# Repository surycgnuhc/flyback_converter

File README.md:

# Flyback Switching Power Supply

Design and simulation work for an isolated flyback switching power supply.

The project is being developed in two stages: a **low-voltage development prototype** for safe simulation and learning, followed by adaptation to the final universal AC input specification.

## Development Prototype Specifications

| Parameter           | Value   |
| ------------------- | ------- |
| Input               | 24 VDC  |
| Output              | 12 V    |
| Output power        | 24 W    |
| Output current      | 2 A     |
| Switching frequency | 100 kHz |
| Efficiency target   | 85%     |
| Regulation          | ±5%     |
| Isolation           | Yes     |

The low-voltage input is being used during the initial flyback design and simulation to avoid working with the high-voltage DC bus produced by an AC mains rectifier.

The output remains fixed at **12 V / 2 A** for this version. An adjustable-output version is planned as a future iteration.

## Final Target Specifications

| Parameter           | Value      |
| ------------------- | ---------- |
| Input               | 90–264 VAC |
| Input frequency     | 60 Hz      |
| Output              | 12 V       |
| Output power        | 24 W       |
| Output current      | 2 A        |
| Switching frequency | 100 kHz    |
| Efficiency target   | 85%        |
| Regulation          | ±5%        |
| Isolation           | Yes        |

The final version will use a universal AC input with a bridge rectifier, bulk capacitor, inrush-current limiting, and isolated flyback converter.

## Project Status

Currently paralleling the design process between kicad and ltspice simulation 

### Low-Voltage Flyback Development

* [ ] Low-voltage input stage — 24 VDC
* [ ] Flyback transformer design
* [ ] Primary-side switch + controller selection
* [ ] Secondary-side rectification + output filtering
* [ ] Feedback/compensation loop
* [ ] Efficiency and regulation validation

### Final AC Input Version

* [x] Bridge rectifier + bulk capacitor front-end — designed and simulated in LTspice
* [ ] Inrush current limiting (NTC/fuse)
* [ ] Adapt flyback design for ~126–373 VDC bus
* [ ] Primary-side switch + controller selection
* [ ] Secondary-side rectification + output filtering
* [ ] Feedback/compensation loop
* [ ] PCB layout

## Repo Structure

```text
/reports   - Written validation summaries with simulation screenshots
/sim       - LTspice schematic (.asc) and simulation files
```

## Reports

* [Rectifier & Bulk Capacitor Stage Validation](reports/rectifier_stage_validation_summary.md)

## Tools

* LTspice (schematic capture and simulation)

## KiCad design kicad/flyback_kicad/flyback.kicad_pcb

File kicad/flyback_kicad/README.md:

# Flyback KiCad project: 24V in, 12V/2A out, 100kHz

Power stage only, ported from the validated LTspice circuit. Made in KiCad 7 format. KiCad 8 and 9 open it and offer to upgrade the files: click Yes.

## Open it
1. Unzip the folder and keep every file together.
2. KiCad > File > Open Project > `flyback.kicad_pro`.
3. Double-click `flyback.kicad_sch` (schematic) or `flyback.kicad_pcb` (board).

## Get to a printable PCB
1. Schematic: double-click T1, set the Footprint field (see gaps below).
2. References (R1, C1 ...) are already set, no annotation needed.
3. PCB Editor: Tools > Update PCB from Schematic (F8) > Update PCB. All footprints and nets load; click to drop them on the board.
4. Place parts, then route with X. Keep GND_PRI and GND_SEC separate.
5. Draw the board outline on layer Edge.Cuts (Place > Line, then close the shape).
6. File > Print, or File > Plot for Gerbers.

## Nets (matches LTspice)
| Net | Pins |
|---|---|
| VIN | J1.1, T1.1 (dot), C3.1, R1.1 |
| GND_PRI | J1.2, J3.2, Q1.S (1-3), R3.2 |
| DRAIN | T1.2, Q1.D (5-8), D2 anode |
| SNUB | D2 cathode, C3.2, R1.2 |
| SEC_AC | T1.4, D1 anode |
| VOUT | D1 cathode, C1+, C2+, J2.1 |
| GND_SEC | T1.3 (dot), C1-, C2-, J2.2 |
| GATE_DRV | J3.1, R2.1 |
| GATE | R2.2, Q1.G (4), R3.1 |

## Parts
| Ref | Part | Footprint |
|---|---|---|
| Q1 | MCQ15N10YA-TP | SOIC-8 (S=1-3, G=4, D=5-8, from MCC datasheet) |
| D1 | 1N5822 Schottky | DO-201AD |
| D2 | UF4007 | DO-41 |
| C1, C2 | 47uF/25V electrolytic | Radial D6.3mm, pin 1 = + |
| C3 | 560nF/100V film | Rect 7.2 x 5.5mm, 5mm pitch |
| R1 | 390 ohm, 5W | Axial power 22.4mm |
| R2, R3 | 10 ohm, 10k | Axial DIN0207 |
| J1, J2 | 2-pin terminal block | 5.08mm |
| J3 | 2-pin header (gate drive in) | 2.54mm |
| T1 | Lp 20.7uH, Np:Ns = 1:1.57 | none yet |

## Known gaps
- T1 has no footprint. Pick one once the core and bobbin are chosen (or a placeholder header for bench wiring).
- No PWM controller, current sense resistor or feedback loop. Gate is driven externally through J3.
- R2 (10 ohm) and R3 (10k) are not in the LTspice simulation yet.
- Q1 is the only SMD part (SOIC-8); everything else is through-hole.
- R1 dissipates about 2.3W at the 30V clamp (30V^2 / 390 ohm), so the 5W part has 2x margin.
- 24V prototype spacing only. The 90-264VAC version needs new creepage and clearance.

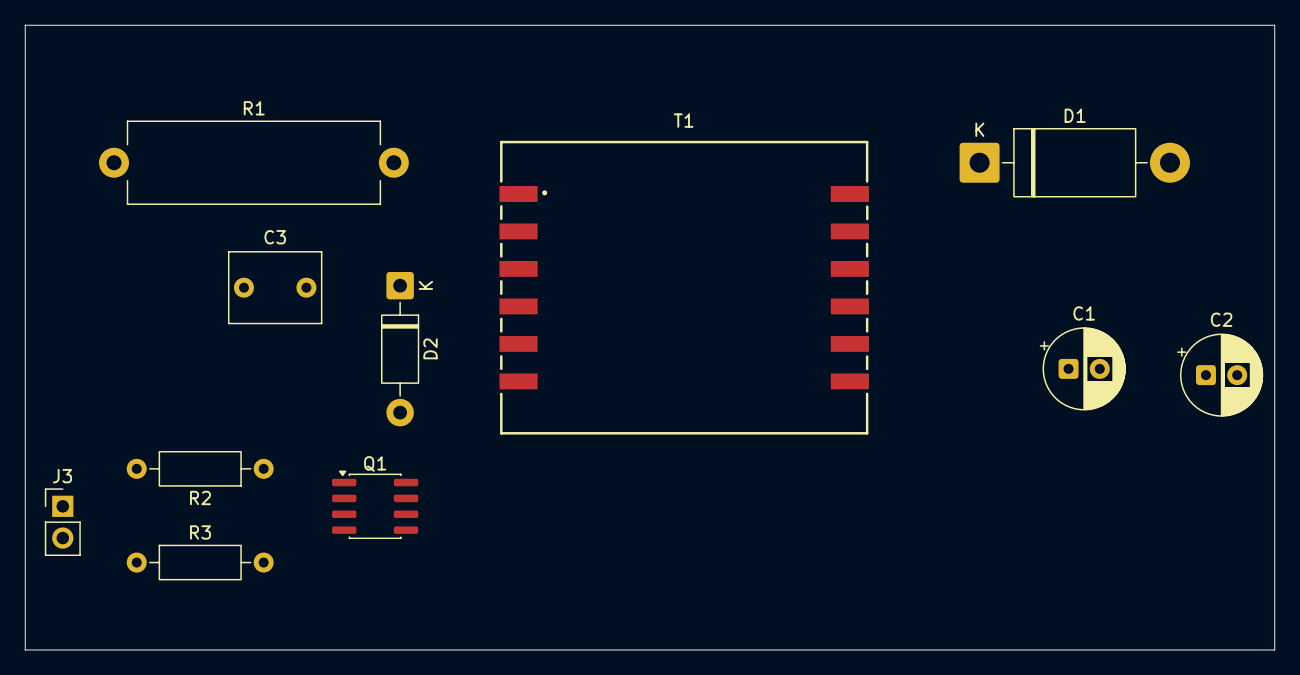
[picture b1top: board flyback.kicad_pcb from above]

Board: 2 copper layers, 100.0 x 50.0 mm, 11 parts (0 on the bottom side), 9 nets, no tracks yet.

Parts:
C1, C2: 47u/25V; CP_Radial_D6.3mm_P2.50mm
C3: 560n/100V film; C_Rect_L7.2mm_W5.5mm_P5.00mm_FKS2_FKP2_MKS2_MKP2
D1: 1N5822; D_DO-201AD_P15.24mm_Horizontal
D2: UF4007; D_DO-41_SOD81_P10.16mm_Horizontal
J3: GATE_DRIVE; PinHeader_1x02_P2.54mm_Vertical
Q1: MCQ15N10YA-TP; SOIC-8_3.9x4.9mm_P1.27mm
R1: 390 5W; R_Axial_Power_L20.0mm_W6.4mm_P22.40mm
R2: 10; R_Axial_DIN0207_L6.3mm_D2.5mm_P10.16mm_Horizontal
R3: 10k; R_Axial_DIN0207_L6.3mm_D2.5mm_P10.16mm_Horizontal
T1: Lp=20.7uH Np:Ns=1:1.57; WE-FB_EFD20

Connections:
/DRAIN: D2.2 (A), Q1.5 (D), Q1.6 (D), Q1.7 (D), Q1.8 (D)
/GATE: Q1.4 (G), R2.2, R3.1
/GATE_DRV: J3.1, R2.1
/GND_PRI: J3.2, Q1.1 (S), Q1.2 (S), Q1.3 (S), R3.2
/GND_SEC: C1.2 (-), C2.2 (-), T1.8
/SEC_AC: D1.2 (A), T1.11
/SNUB: C3.2, D2.1 (K), R1.2
/VIN: C3.1, R1.1
/VOUT: C1.1 (+), C2.1 (+), D1.1 (K)
